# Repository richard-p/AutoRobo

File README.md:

# AutoRobo
A brief foray into state space control systems.

<b>PHASE ONE</b>

First Go (Finished: 1, 2, x)
1)  Im working on normal control first to get my feet wet.
    Currently Im designing a remote to control my robot.
      * SPI OLED display for remote visuals
      * nRF24L01 SPI radio for transmission
      * joystick module for direction
      * seeeduino xiao for control (for initial tests an Arduino Mega was used)

    Board design is also uploaded.
    
2) Integrate receiving nRF24 into robot. Mock up is already
   live to test remote.
      * Arduino Uno - needed to use software SPI because motordriver uses hardware SPI for nonSPI purposes.
      * nRF24L01

3) Write control algorithm for robot.
      * Y position on joystick to control forward/backward speed
      * X position on joystick to control left/right
      * Display to show intended direction of motion with an arrow on remote

The robot body contains a Seeedstudio motordriver v2, Arduino Uno, and Arduino prototype shield (on which lies the nRF).

<b>PHASE TWO</b>

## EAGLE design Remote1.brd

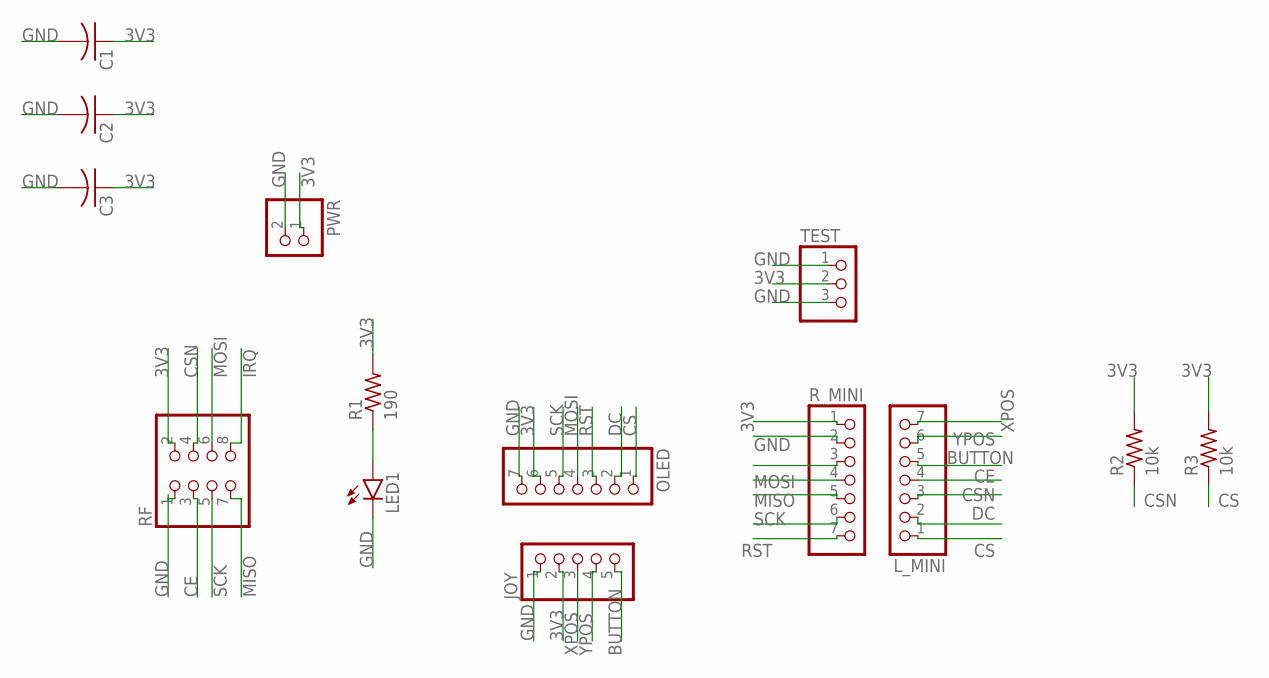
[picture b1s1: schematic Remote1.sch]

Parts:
C1, C2, C3: C-US025-024X044; C025-024X044
JOY: PINHD-1X5/90; 1X05/90
LED1: LED5MM
L_MINI: PINHD-1X7; 1X07
OLED: PINHD-1X7; 1X07
PWR: PINHD-1X2; 1X02
R1: 190; 0204/7
R2, R3: 10k; 0204/7
RF: PINHD-2X4; 2X04
R_MINI: PINHD-1X7; 1X07
TEST: PINHD-1X3; 1X03

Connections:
3V3: C1.1, C2.1, C3.1, JOY.2, OLED.6, PWR.1, R1.2, R2.2, R3.2, RF.2, R_MINI.1, TEST.2
BUTTON: JOY.5, L_MINI.5
CE: L_MINI.4, RF.3
CS: L_MINI.1, OLED.1, R3.1
CSN: L_MINI.3, R2.1, RF.4
DC: L_MINI.2, OLED.2
GND: C1.2, C2.2, C3.2, JOY.1, LED1.K (C), OLED.7, PWR.2, RF.1, R_MINI.2, TEST.1, TEST.3
IRQ: RF.8
MISO: RF.7, R_MINI.5
MOSI: OLED.4, RF.6, R_MINI.4
unnamed: LED1.A, R1.1
RST: OLED.3, R_MINI.7
SCK: OLED.5, RF.5, R_MINI.6
XPOS: JOY.3, L_MINI.7
YPOS: JOY.4, L_MINI.6

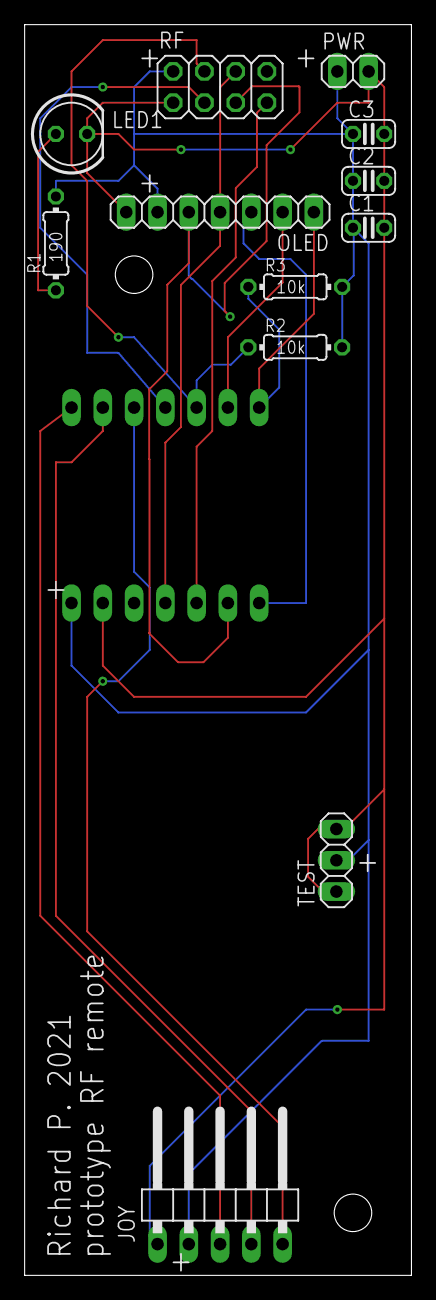
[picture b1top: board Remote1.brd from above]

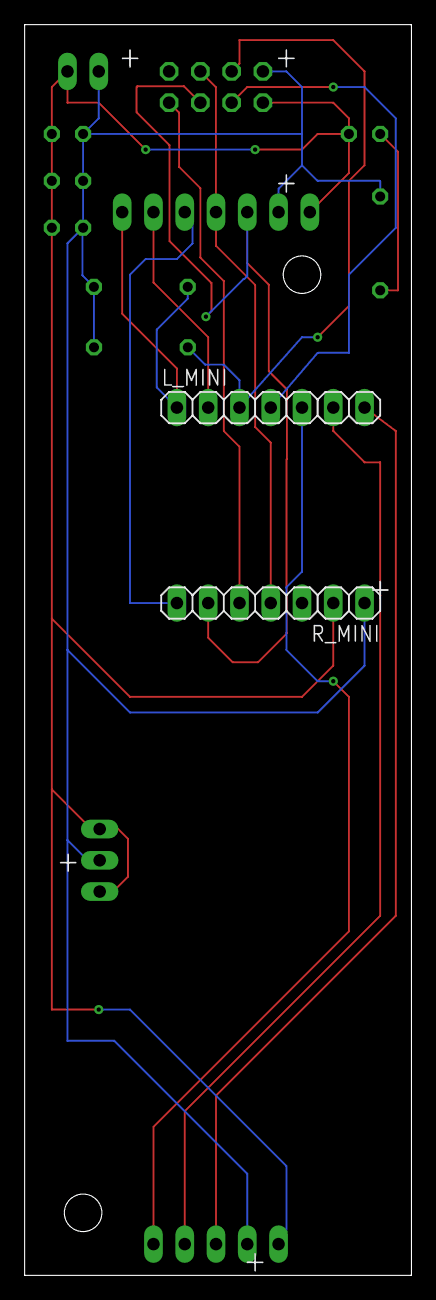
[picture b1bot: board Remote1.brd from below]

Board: 2 copper layers, 31.4 x 101.6 mm, 14 parts (2 on the bottom side), 14 nets.

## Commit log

2019-05-22 First commit, saving initial transmit files- one way
2019-05-29 Update: communicate in both directions (untested)
2021-11-02 Add files via upload
    nRFreceiver is the remote test receiver
    remoteControlTest is the initial iteration of testing but with I2C OLED
    remoteControlTestSPI is the testing done after deciding to switch to all SPI for reduction of necessary pins for XIAO
2021-11-02 Update README.md
    added clarity
2021-11-02 Add files via upload
    Schematic and board files for remote.
